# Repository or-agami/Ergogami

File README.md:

# Ergogami Keyboard
This keyboard powered by [ZMK](https://github.com/zmkfirmware/zmk), PCB board layout generated with [Ergogen](https://github.com/ergogen/ergogen), Gerber files generated with [KiCad](https://www.kicad.org/).

Ergogami keyboard is a fully wireless split keyboard with 36 keys (Each half has 15 main keys and 3 thumb keys).

## Why:
I realized that I'm moving my fingers away from the homebrow a lot in "regular" keyboards and I tried to make a keyboard with minimal movement without compromise the keys behavior

## How:
[Ergogami ZMK-Config](https://github.com/or-agami/zmk-config-ergogami)

[Ergogami Ergogen files](https://github.com/or-agami/ergogen)

<!-- ## Instructions for ordering
See in [Wiki Page](https://github.com/or-agami/Ergogami/wiki) -->

## Photos

<!-- 
## Credits
...
-->

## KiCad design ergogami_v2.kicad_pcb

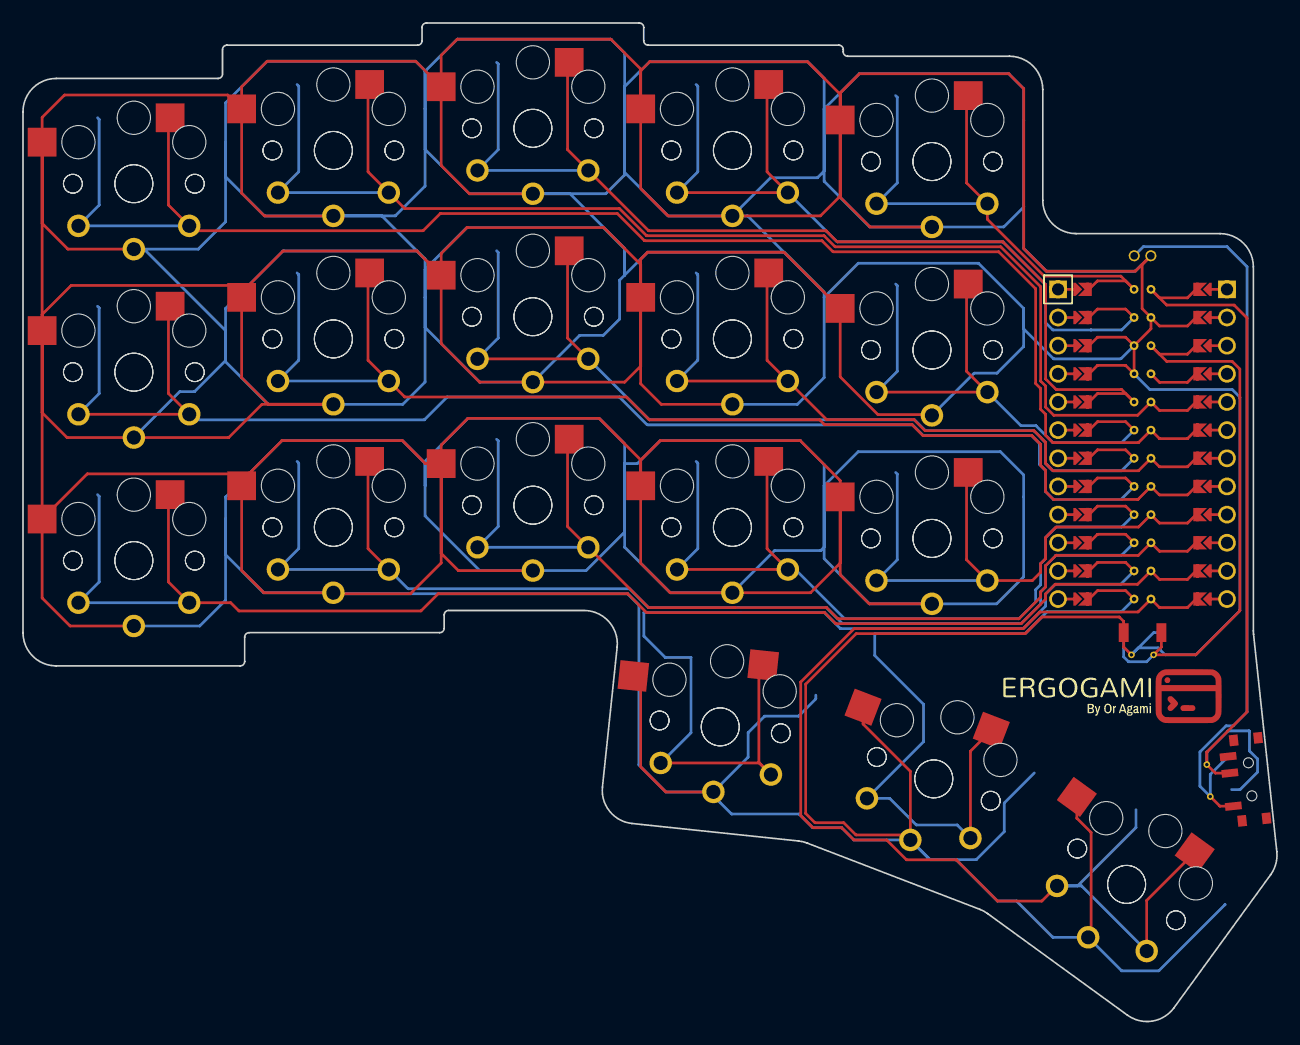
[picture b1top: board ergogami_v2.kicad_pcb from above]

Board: 2 copper layers, 113.1 x 90.1 mm, 37 parts (0 on the bottom side), 19 nets.

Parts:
MCU1: ProMicro
S1, S2, S3, S4, S5, S6, S7, S8, S9, S10, S11, S12, S13, S14, S15, S16, S17, S18, S19, S20, S21, S22, S23, S24, S25, S26, S27, S28, S29, S30, S31, S32, S33, S34, S35, S36: PG1350

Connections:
GND: MCU1.2, MCU1.21, MCU1.22, S1.2, S2.2, S3.2, S4.2, S5.2, S6.2, S7.2, S8.2, S9.2, S10.2, S11.2, S12.2, S13.2, S14.2, S15.2, S16.2, S17.2, S18.2, S19.2, S20.2, S21.2, S22.2, S23.2, S24.2, S25.2, S26.2, S27.2, S28.2, S29.2, S30.2, S31.2, S32.2, S33.2, S34.2, S35.2, S36.2
P0: MCU1.23, S23.1, S24.1
P1: MCU1.24, S29.1, S30.1
P2: MCU1.20, S17.1, S18.1
P3: MCU1.19, S27.1, S28.1
P4: MCU1.18, S15.1, S16.1
P5: MCU1.17, S3.1, S4.1
P6: MCU1.16, S19.1, S20.1
P7: MCU1.15, S7.1, S8.1
P8: MCU1.14, S31.1, S32.1
P9: MCU1.13, S33.1, S34.1
P10: MCU1.12, S35.1, S36.1
P14: MCU1.10, S13.1, S14.1
P15: MCU1.9, S25.1, S26.1
P16: MCU1.11, S1.1, S2.1
P18: MCU1.8, S9.1, S10.1
P19: MCU1.7, S21.1, S22.1
P20: MCU1.6, S5.1, S6.1
P21: MCU1.5, S11.1, S12.1

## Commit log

2022-06-02 Rename ergogami_v2.kicad_pcb to PCB/ergogami_v2.kicad_pcb
